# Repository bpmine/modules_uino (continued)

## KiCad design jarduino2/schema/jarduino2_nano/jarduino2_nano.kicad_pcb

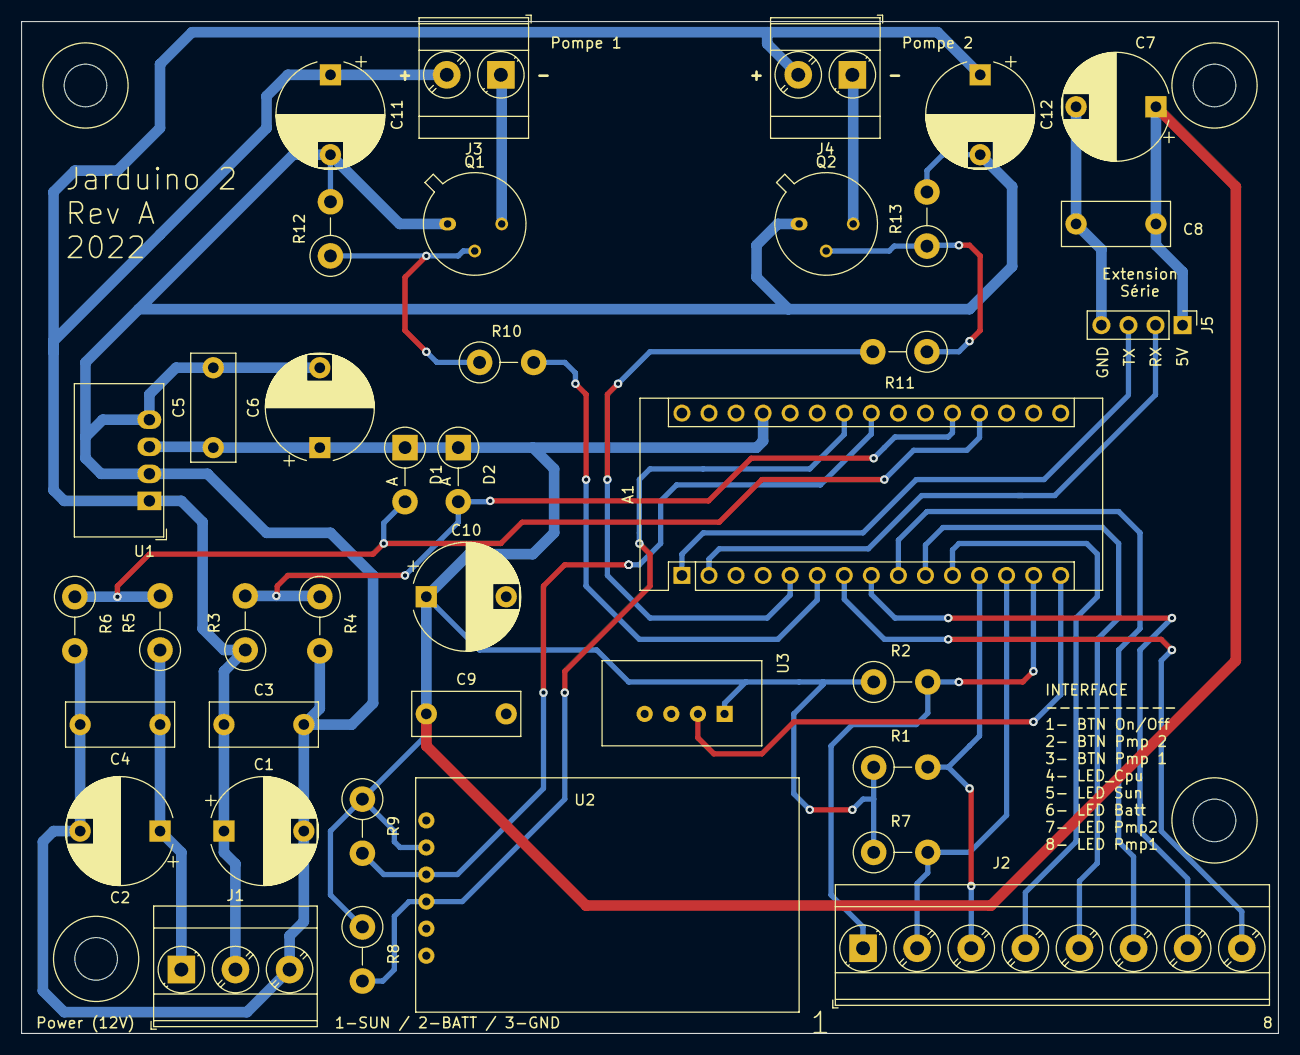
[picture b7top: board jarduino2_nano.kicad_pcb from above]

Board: 2 copper layers, 118.0 x 95.0 mm, 38 parts (0 on the bottom side), 25 nets.

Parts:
A1: Arduino_Nano_v3.x; Arduino_Nano
C1, C2, C6, C7, C10, C11, C12: 50µF / 50V; CP_Radial_D10.0mm_P7.50mm
C3, C4, C5, C8, C9: 1nF / 50V; C_Rect_L10.0mm_W4.0mm_P7.50mm_MKS4
D1, D2: D_Schottky; D_DO-15_P5.08mm_Vertical_AnodeUp
J1: Power; TerminalBlock_Phoenix_MKDS-3-3-5.08_1x03_P5.08mm_Horizontal
J2: Interface; TerminalBlock_Phoenix_MKDS-3-8-5.08_1x08_P5.08mm_Horizontal
J3: Pompe 1; TerminalBlock_Phoenix_MKDS-3-2-5.08_1x02_P5.08mm_Horizontal
J4: Pompe 2; TerminalBlock_Phoenix_MKDS-3-2-5.08_1x02_P5.08mm_Horizontal
J5: Ext Ser; PinHeader_1x04_P2.54mm_Vertical
Q1, Q2: Q_NPN_BCE; TO-39-3
R1, R2, R3, R5, R7, R12, R13: 100k; R_Axial_DIN0411_L9.9mm_D3.6mm_P5.08mm_Vertical
R4, R6: 40k; R_Axial_DIN0411_L9.9mm_D3.6mm_P5.08mm_Vertical
R8, R9: 10k; R_Axial_DIN0411_L9.9mm_D3.6mm_P5.08mm_Vertical
R10, R11: 220; R_Axial_DIN0411_L9.9mm_D3.6mm_P5.08mm_Vertical
U1: RFB-0505S; Converter_DCDC_Murata_MEE3SxxxxSC_THT
U2: RtcArduino; BPC_RtcArduino
U3: DHT22; BPC_DHT22

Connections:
+5V: A1.27, C5.1, C6.1, C7.1, C8.1, C9.1, C10.1, D1.1, D2.1, J5.1, R1.1, R2.1, R7.1, R8.1, R9.1, U1.3, U2.2, U3.1
+12V: C1.1, C3.1, C11.1, C12.1, J1.2, J3.2, J4.2, R3.1, U1.1
BTN_ONOFF: A1.14, J2.1, R2.2
BTN_PMP1: A1.12, J2.3, R1.2
BTN_PMP2: A1.13, J2.2, R7.2
CMD_PMP1: A1.6, R10.2
CMD_PMP2: A1.5, R11.2
GND: A1.4, A1.29, C1.2, C2.2, C3.2, C4.2, C5.2, C6.2, C7.2, C8.2, C9.2, C10.2, C11.2, C12.2, J1.3, J5.4, Q1.1, Q2.1, R4.2, R6.2, R12.2, R13.2, U1.2, U1.4, U2.1, U3.4
LED_12V_BATT: A1.9, J2.6
LED_12V_SUN: A1.10, J2.5
LED_CPU: A1.11, J2.4
LED_PMP1: A1.7, J2.8
LED_PMP2: A1.8, J2.7
unnamed: A1.1, J5.3
unnamed: A1.2, J5.2
unnamed: A1.15, U3.2
unnamed: C2.1, C4.1, J1.1, R5.1
unnamed: J3.1, Q1.3
unnamed: J4.1, Q2.3
unnamed: Q1.2, R10.1, R12.1
unnamed: Q2.2, R11.1, R13.1
POW_BATT: A1.20, D2.2, R3.2, R4.1
POW_SUN: A1.19, D1.2, R5.2, R6.1
SCL: A1.24, R8.2, U2.4
SDA: A1.23, R9.2, U2.3
